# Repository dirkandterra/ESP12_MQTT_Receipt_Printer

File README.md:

# ESP-12 MQTT Receipt Printer

Controls a generic 58mm ESC/POS thermal printer over UART from an ESP-12 (ESP8266) module. Subscribes to an MQTT topic and prints any message received.

## Hardware

| Signal | ESP-12 pin | Notes |
|--------|-----------|-------|
| UART TX | GPIO2 (UART1) | Connect to printer RX |
| GND | GND | Common ground with printer |

UART1 on ESP8266 is TX-only (GPIO2), which is sufficient — ESC/POS printers do not require RX for normal printing.

Printer power: most 58mm printers need 5–9 V at up to 2 A. Do **not** power from the ESP module.

## Configuration

Copy `main/secret.h.example` to `main/secret.h` and fill in your credentials:

```c
#define WIFI_SSID      "your_ssid"
#define WIFI_PWD       "your_password"
#define MQTT_SERVER    "your.broker.ip"
#define MOSQUITTO_USR  "username"
#define MOSQUITTO_PWD  "password"
```

The MQTT topic is defined in `main/main.c`:
```c
const char *mqtt_topic = "ESP12_Receipt/print";
```

Printer settings (UART port, baud rate) are in `idf.py menuconfig` → Receipt Printer.

## Build

Requires [ESP8266_RTOS_SDK](https://github.com/espressif/ESP8266_RTOS_SDK) v3.4 or later.

```bash
export IDF_PATH=/path/to/ESP8266_RTOS_SDK
idf.py build
idf.py -p /dev/ttyUSB0 flash
```

## Behaviour

- On boot, the IP address is printed on the receipt paper.
- Any message published to the MQTT topic is printed in Font B (condensed).
- WiFi: retries 5 times on disconnect, then pauses 5 minutes before trying again.
- MQTT: auto-reconnects indefinitely; re-subscribes on each reconnect.

## Project structure

```
main/
  main.c            WiFi init, MQTT topic, app entry
  printer.c/.h      ESC/POS UART driver
  mqtt_printer.c/.h MQTT subscriber → printer
  secret.h          WiFi & MQTT credentials (not in repo)
```

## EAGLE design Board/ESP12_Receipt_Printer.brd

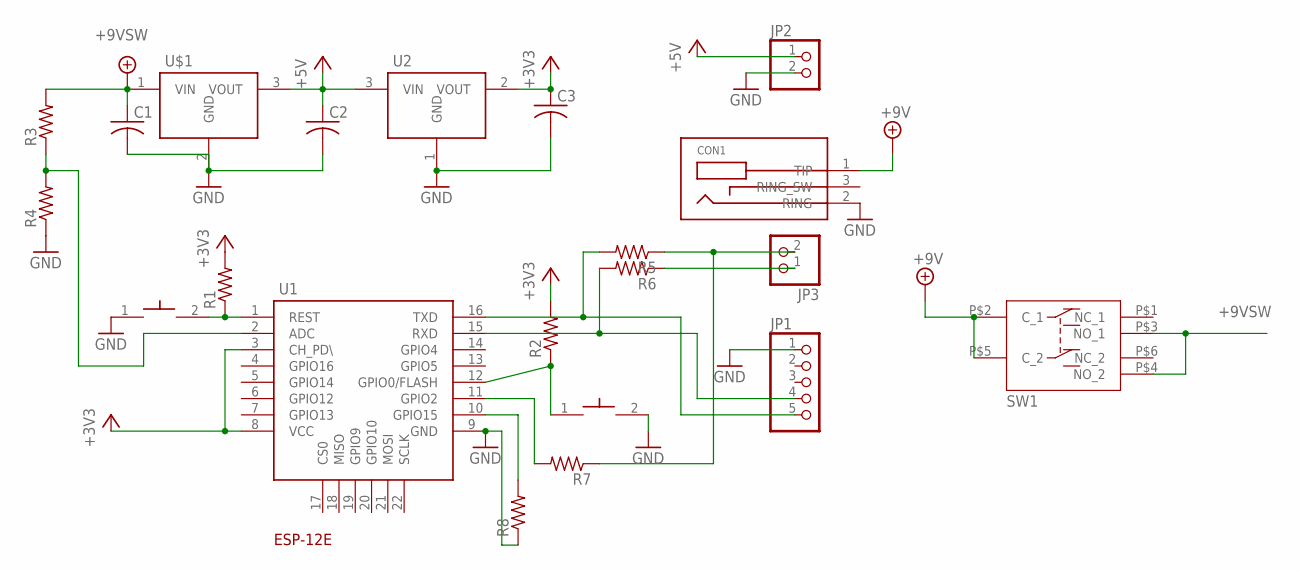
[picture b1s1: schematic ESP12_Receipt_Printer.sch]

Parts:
BTN1, BTN2: FSMSM_SWITCH_6X3.6; SMD-2-SWITCH
C1, C2, C3: C-USC0805; C0805
CON1: BARREL_JACK_3PINPJ-102A_2MM_HOLES; PJ-102A_2MM_HOLES
JP1: PINHD-1X5/90; 1X05/90
JP2, JP3: PINHD-1X2/90; 1X02/90
R1, R2, R3, R4, R5, R6, R7, R8: R-US_M0805; M0805
SW1: SW_TOGGLE_6PIN_DPDT; BTN_6PIN
U1: ESP-12E
U2: AMS1117; SOT223
U$1: 7805; TO252-3

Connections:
+3V3: C3.1, R1.2, R2.2, U1.3 (CH_PD\), U1.8 (VCC), U2.2 (VOUT)
+5V: C2.1, JP2.1, U2.3 (VIN), U$1.3 (VOUT)
+9VSW: C1.1, R3.2, SW1.P$3 (NO_1), SW1.P$4 (NO_2), U$1.1 (VIN)
+9V_SW: CON1.1 (TIP), SW1.P$2 (C_1), SW1.P$5 (C_2)
GND: BTN1.2, BTN2.1, C1.2, C2.2, C3.2, CON1.2 (RING), JP1.1, JP2.2, R4.1, R8.1, U1.9 (GND), U2.1 (GND), U$1.2 (GND)
unnamed: BTN1.1, R2.1, U1.12 (GPIO0/FLASH)
unnamed: BTN2.2, R1.1, U1.1 (REST)
unnamed: JP1.4, R6.2, U1.15 (RXD)
unnamed: JP1.5, R5.2, U1.16 (TXD)
unnamed: R3.1, R4.2, U1.2 (ADC)
unnamed: JP3.1, R6.1
unnamed: R8.2, U1.10 (GPIO15)
unnamed: R7.2, U1.11 (GPIO2)
unnamed: JP3.2, R5.1, R7.1

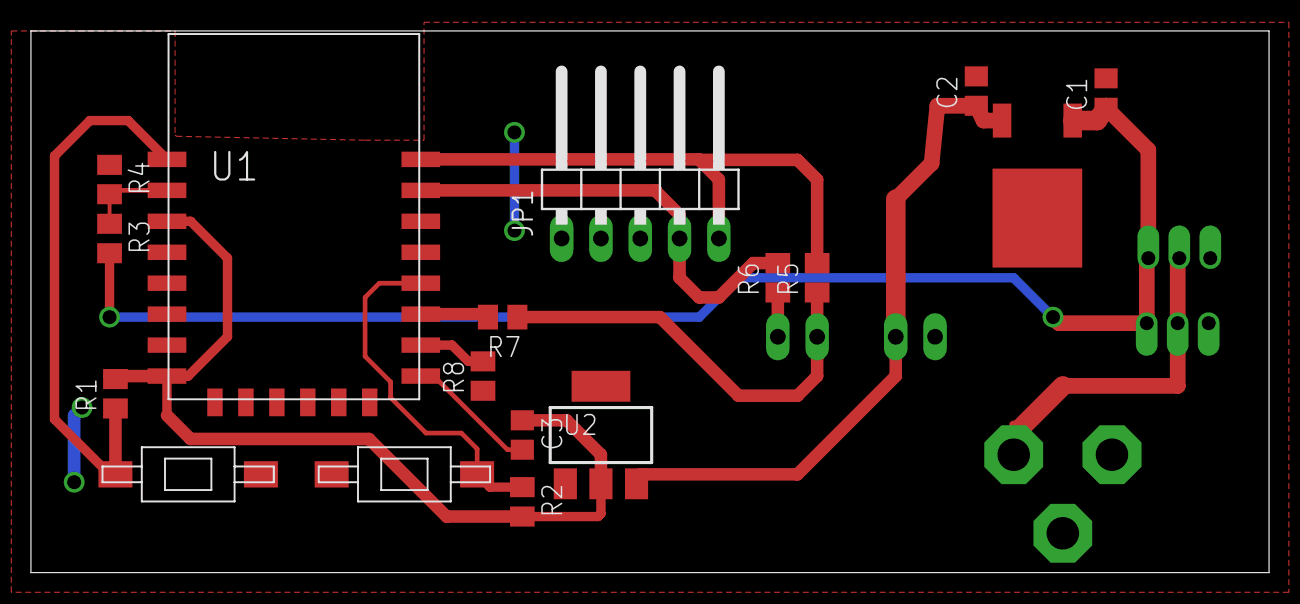
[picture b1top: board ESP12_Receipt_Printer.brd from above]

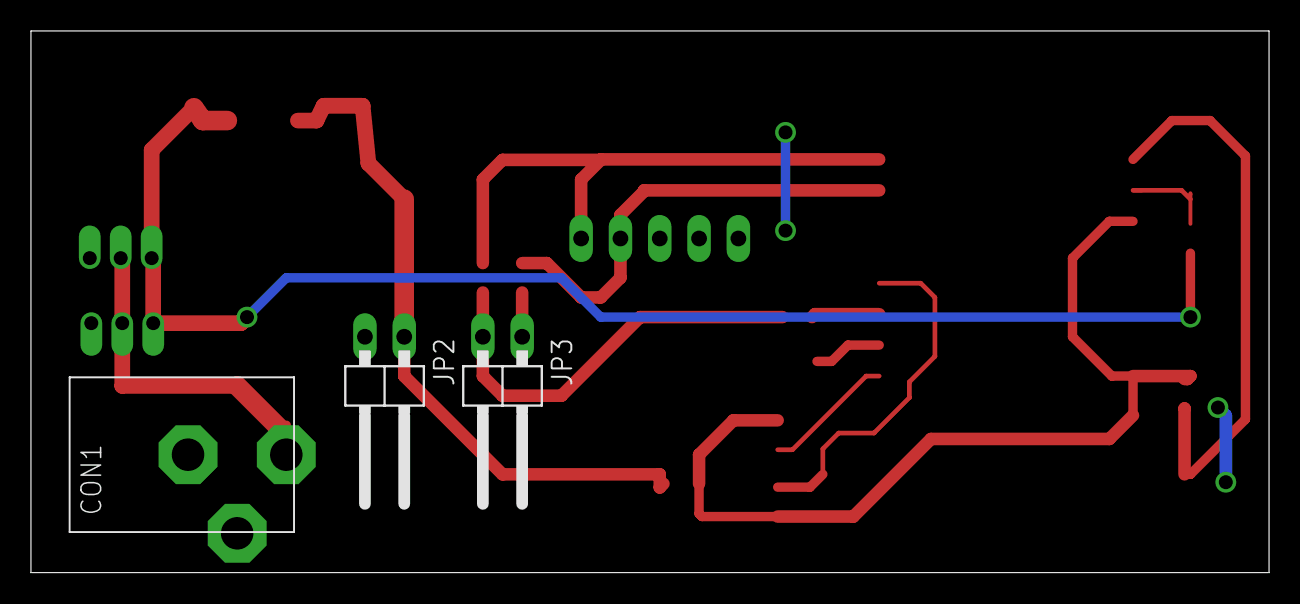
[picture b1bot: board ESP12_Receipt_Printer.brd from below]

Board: 2 copper layers, 80.0 x 35.0 mm, 21 parts (3 on the bottom side), 14 nets.

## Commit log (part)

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2026-05-30 Added board files
